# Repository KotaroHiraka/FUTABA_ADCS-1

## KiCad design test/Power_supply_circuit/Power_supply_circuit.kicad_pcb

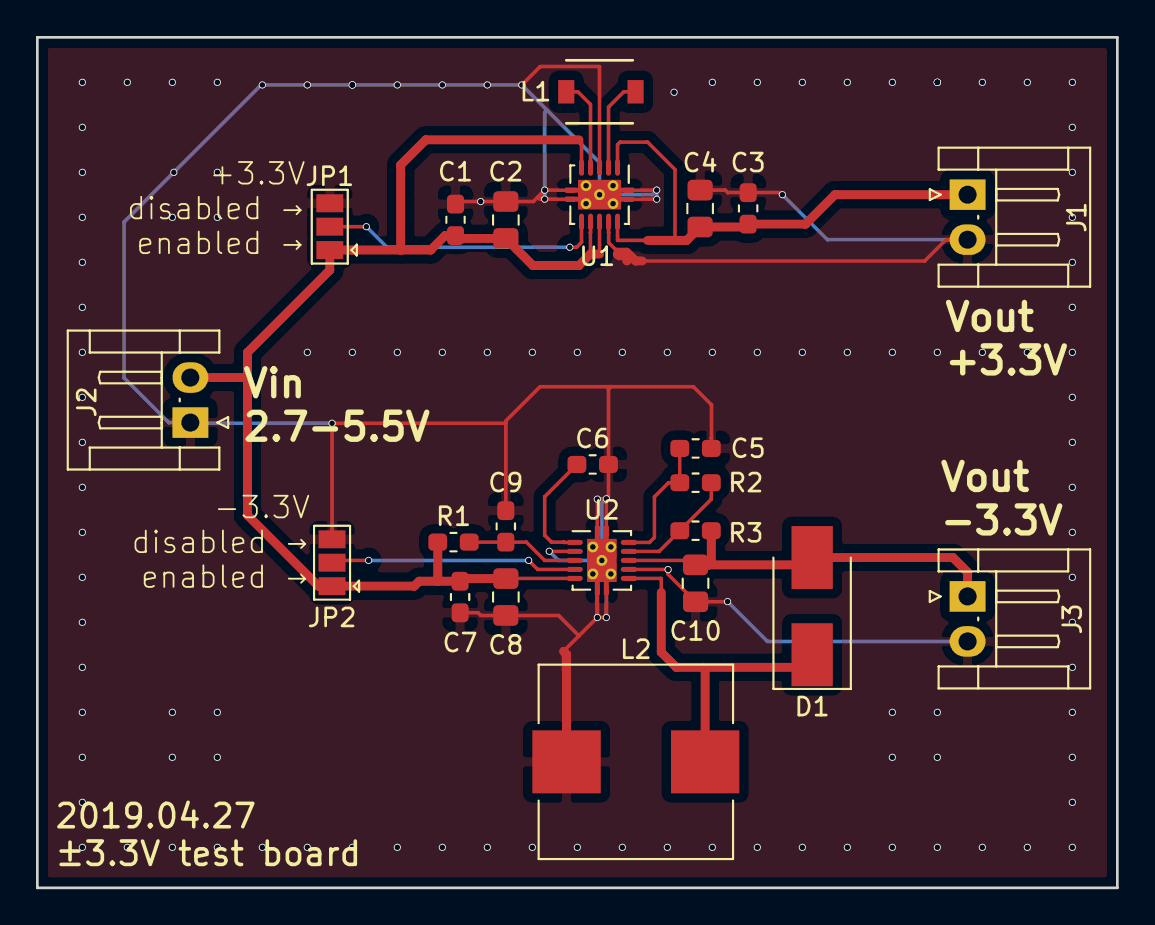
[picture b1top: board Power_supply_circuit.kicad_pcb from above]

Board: 2 copper layers, 60.0 x 47.2 mm, 23 parts (0 on the bottom side), 13 nets.

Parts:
C1, C3, C7, C9: 0.1u; C_0603_1608Metric_Pad1.05x0.95mm_HandSolder
C2, C4, C8: 10u; C_0805_2012Metric_Pad1.15x1.40mm_HandSolder
C5: 0.22u; C_0603_1608Metric_Pad1.05x0.95mm_HandSolder
C6: 4700p; C_0603_1608Metric_Pad1.05x0.95mm_HandSolder
C10: 22u; C_0805_2012Metric_Pad1.15x1.40mm_HandSolder
D1: SL23-E3/52T; D_SMB_Handsoldering
J1: +3.3V; JST_EH_S02B-EH_1x02_P2.50mm_Horizontal
J2: Vin; JST_EH_S02B-EH_1x02_P2.50mm_Horizontal
J3: -3.3V; JST_EH_S02B-EH_1x02_P2.50mm_Horizontal
JP1, JP2: EN; SolderJumper-3_P1.3mm_Open_Pad1.0x1.5mm
L1: 2.2u; inductor_VLF4012-2R2
L2: 4.7u; L_Wuerth_HCI-1030
R1: 100; R_0603_1608Metric_Pad1.05x0.95mm_HandSolder
R2: 100k; R_0603_1608Metric_Pad1.05x0.95mm_HandSolder
R3: 270k; R_0603_1608Metric_Pad1.05x0.95mm_HandSolder
U1: TPS63000; Texas_S-PVSON-N10_ThermalVias
U2: TPS63700; Texas_S-PVSON-N10_ThermalVias

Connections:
+3V3: C3.1, C4.1, J1.1, U1.1, U1.10
+BATT: C1.1, C2.1, C7.1, C8.1, J2.2, JP1.1, JP2.1, R1.1, U1.5, U1.7, U1.8, U2.5
-3V3: C10.1, D1.2, J3.1, R3.2, U2.8
GND: C1.2, C2.2, C3.2, C4.2, C5.1, C6.2, C7.2, C8.2, C9.2, C10.2, J1.2, J2.1, J3.2, JP1.3, JP2.3, L2.2, U1.3, U1.9, U1.11, U2.2, U2.7, U2.11
unnamed: C5.2, R2.1, U2.10
unnamed: C6.1, U2.1
unnamed: C9.1, R1.2, U2.3
unnamed: D1.1, L2.1, U2.6
unnamed: JP1.2, U1.6
unnamed: JP2.2, U2.4
unnamed: L1.1, U1.4
unnamed: L1.2, U1.2
unnamed: R2.2, R3.1, U2.9

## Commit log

2019-07-02 Create gyro_CRM_test
2019-07-02 ジャイロと通信できるようになった
2019-07-03 動作確認済
2019-07-03 create library
    ライブラリ化
    受信データのchecksum計算は未実装
2019-07-11 データを連続出力するようにした
2019-07-15 標準出力先を追加
2019-07-16 Add EAGLE EM_ver1
2019-07-18 Add Lecture
2019-07-20 サンプリングレートを50Hzに固定
